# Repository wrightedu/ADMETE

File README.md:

# Assured Digital Microelectronics Education & Training Ecosystem : ADMETE

The ADMETE lab (348 Russ Engineering) seeks to develop a pipeline of engineering students with skills in microelectronics design, testing, and hardware security.  In this lab we use industry standard prototyping equipment to manufacture and test printed circuit boards (PCBs).

This document serves to outline the equipment and processes available to students within the ADMETE space and in related labs.  

## ADMETE Equipment

Below is a list of all ADMETE equipment available in 348 Russ.

---

### ProtoMat E44 PCB Milling Machine

For performing Milling and drilling procedures on 1 and 2 sided circuit boards, the LPKF Protomat E44 can mill with +/- 0.02mm accuracy and +/- 0.005mm repeatability.  The E44 supports partial rubout (copper removal) and up to 8-layer boards with our additional heated press.  The primary purpose fo these machines is training in the basics of PCB prototyping and manufacturing limitations.

* [E44 manual](./docs/LPKF_E44_guide.pdf)
* [E44 user guide (WSU created)](./guides/e44.md)

---

### ProtoMat S64 PCB Milling Machine

Supports much of the same processes as the e44 but with automated tool changes, the LPKF Protomat S64 speeds up the prototyping process.  Used in conjunction with the ProtoLaser U4, the S64 is the ideal system for drilling through-holes, vias, fiducials (alignemtn holes), and for contour routing thhe board outline to remove it from the PCB material.

* [S64 manual](./docs/LPKF_S64_guide.pdf)
* [S64 user guide (WSU created)](./guides/s64.md)

---

### ProtoLaser U4

The ProtoLaser U4 is a 355nm UV laser based milling system allowing for much finer structures (50 micrometer line width, 15 micrometer separatation).  This system significantly speeds up the PCB prototyping process and allows for more precise and compact packaging of devices.

The LPKF laser system is one of the key pieces of this lab as it is an industry standard PCB prototyping system used in many aviation, space, and electronics companies

* [ProtoLaser U4 manual](./docs/)
* [ProtoLaser U4 user guide (WSU created)](./guides/)

---

### Contac S4 Through-hole Plater

The Contac S4 through hole plater uses a electroplating process to make electronic connections in between layers of the circuit board.  This allows for denser packaging of components while maintaining the required logical / electrical connections between devices.

* [Contac S4manual](./docs/)
* [Contac S4 user guide (WSU created)](./guides/contac_s4.md)

---

### ProtoPlace E4 Pick and Place Machine

The ProtoPlace E4 allows for quick and easy component placement of small sized surface-mount devices (SMD's), significantly speeding up prototyping compared to manual placement with tweezers.

* [ProtoPlace E4 manual](./docs/)
* [ProtoPlace E4 user guide (WSU created)](./guides/)

---

### ProtoFlow S4 Reflow Oven

The ProtoFlow S4 reflow oven allows students to use surface-mount devices and solder paste to attach chips and devices to their circuit board.  This reflow oven is software controlled to adhere to a strict thermal process for optimal lead-free solder application.

* [ProtoFlow S4 manual](./docs/)
* [ProtoFlow S4 user guide (WSU created)](./guides/)

---

### UV LED Solder Mask Curing Station

The UV curing station allows the application of a solder-resist mask of acrylic paint be added to a circuit board.  When used in conjunction with a solder mask printed on transparency material, the UV curing station allows selective curing of the acrylic solder-resist paint so that any necessary electricl connections can be later exposed for device placement.

* [UV curing manual](./docs/)
* [UV curing user guide (WSU created)](./guides/)

---

### Environmental Chamber (located in Electronic Materials Lab: 116 Russ Engineering)

The TestEquity Environmental Chamber is a device that allows us to test microelectronics in a variety of conditions by altering the ambient temperature and humidity of the chamber.  This allows for hot/cold/humid/dry testing of microelectronics with the potential to incite failures that may lead to security vulnerabilities. 

* [TestEquity Enviro Chamber manual](./docs/)
* [Enviro Chamber user guide (WSU created)](./guides/)

---

### Equipment Template

Paragraph

* [manual](./docs/)
* [user guide (WSU created)](./guides/)

---

### ALL PROCEDURES AND PROTOCOLS ARE SUBJECT TO CHANGE

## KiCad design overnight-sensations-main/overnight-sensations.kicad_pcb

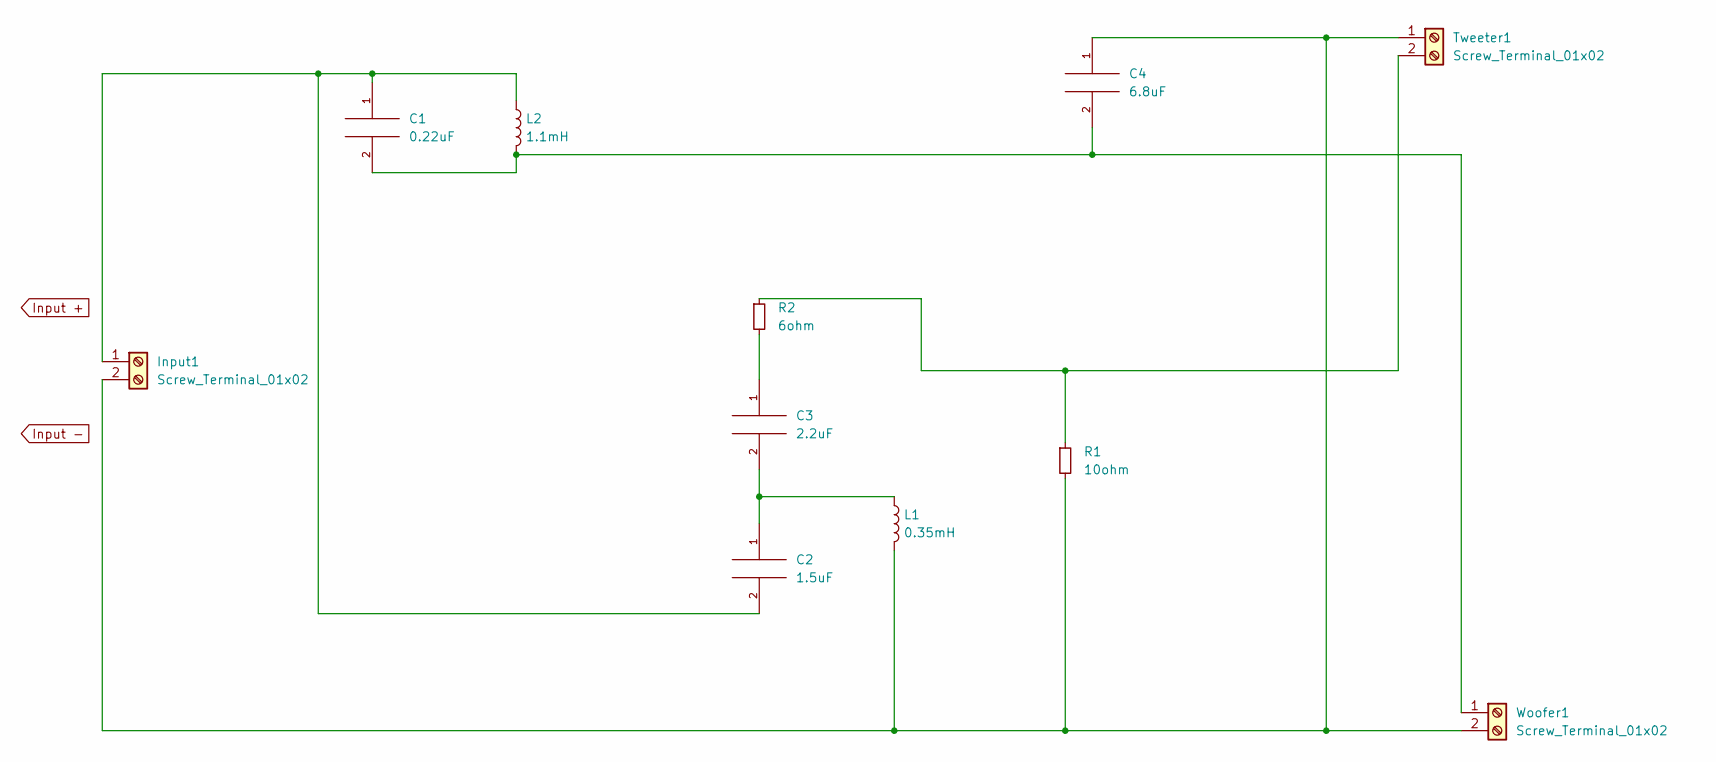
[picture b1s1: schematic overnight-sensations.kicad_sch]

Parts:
C1: 0.22uF; C_Axial_L19.0mm_D7.5mm_P25.00mm_Horizontal
C2: 1.5uF; CP_Axial_L37.0mm_D13.0mm_P43.00mm_Horizontal
C3: 2.2uF; CP_Axial_L37.0mm_D13.0mm_P43.00mm_Horizontal
C4: 6.8uF; CP_Axial_L46.0mm_D20.0mm_P52.00mm_Horizontal
Input1: Screw_Terminal_01x02; TerminalBlock_Phoenix_MKDS-1,5-2-5.08_1x02_P5.08mm_Horizont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
L1: 0.35mH; L_Toroid_Vertical_L31.8mm_W15.9mm_P13.50mm_Bourns_5700
L2: 1.1mH; L_Toroid_Horizontal_D41.9mm_P37.60mm_Vishay_TJ7
R1: 10ohm; R_Axial_Power_L48.0mm_W12.5mm_P55.88mm
R2: 6ohm; R_Axial_Power_L48.0mm_W12.5mm_P55.88mm
Tweeter1: Screw_Terminal_01x02; TerminalBlock_Phoenix_MKDS-1,5-2-5.08_1x02_P5.08mm_Horizont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
Woofer1: Screw_Terminal_01x02; TerminalBlock_Phoenix_MKDS-1,5-2-5.08_1x02_P5.08mm_Horizont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

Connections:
unnamed: C2.1, C3.2, L1.1
unnamed: C1.1, C2.2, Input1.1, L2.1
unnamed: C4.1, Input1.2, L1.2, R1.2, Tweeter1.1, Woofer1.2
unnamed: R1.1, R2.1, Tweeter1.2
unnamed: C3.1, R2.2
unnamed: C1.2, C4.2, L2.2, Woofer1.1

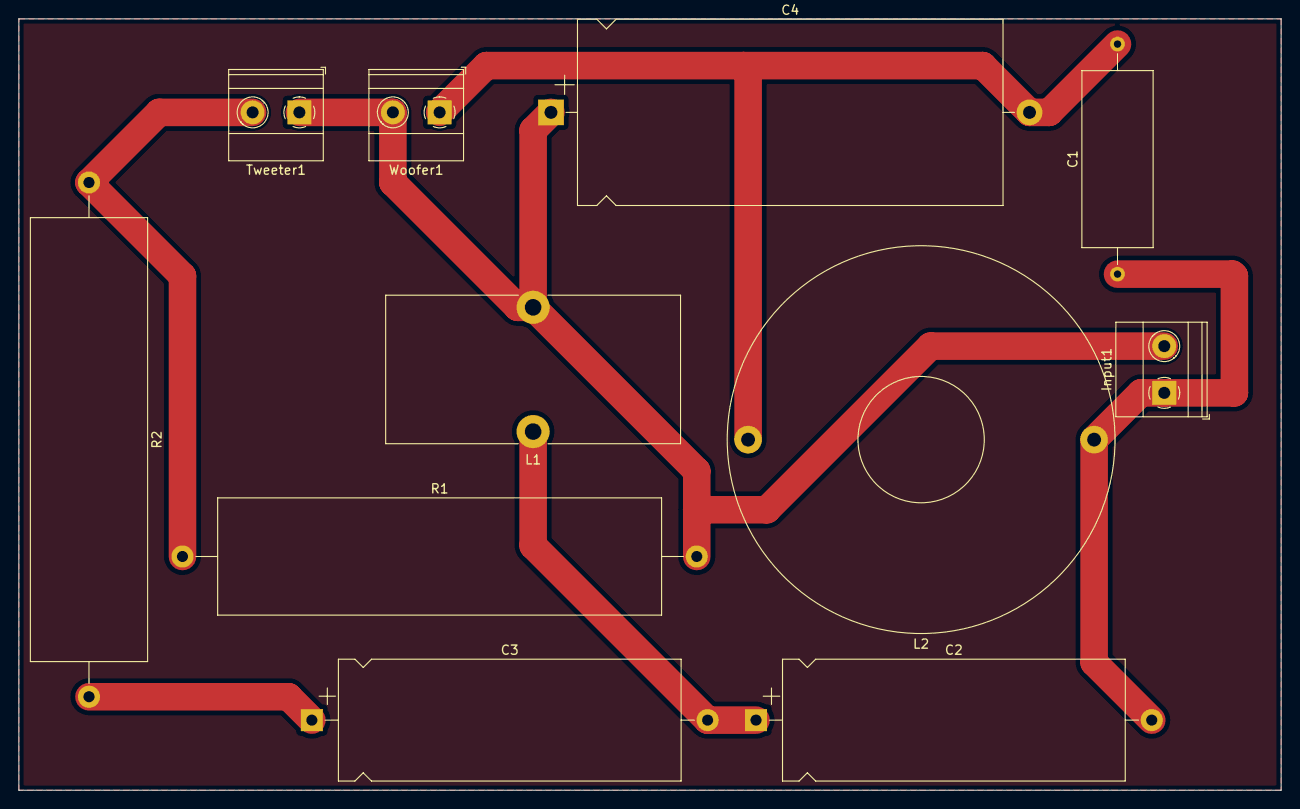
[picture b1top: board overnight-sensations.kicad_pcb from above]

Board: 2 copper layers, 137.2 x 83.8 mm, 11 parts (0 on the bottom side), 6 nets.

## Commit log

2023-02-17 Uploaded Matt's overnight-sensations
2023-02-22 Added E44 Guide
2024-06-25 adding pics
2024-06-25 adding guides and writeups e44 and s64
2024-06-25 massive updates
